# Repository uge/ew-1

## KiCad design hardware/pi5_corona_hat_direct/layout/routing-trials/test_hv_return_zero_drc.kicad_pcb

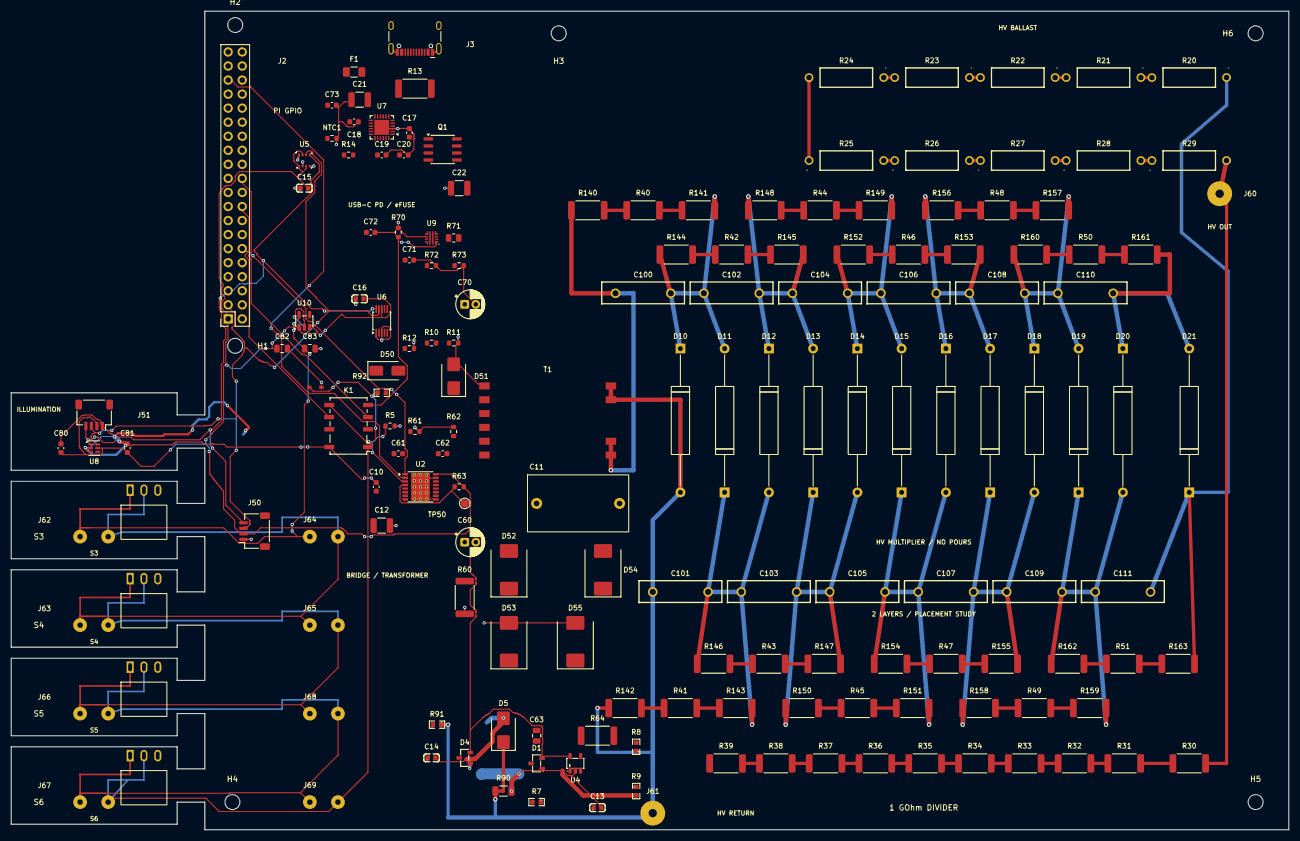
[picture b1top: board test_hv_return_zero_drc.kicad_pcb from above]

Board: 2 copper layers, 231.0 x 148.0 mm, 175 parts (0 on the bottom side), 108 nets.

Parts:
C10: 100nF 50V X7R 10%; C_0603_1608Metric
C11: 120nF 100V; Film_KYET_18x10mm_P15mm
C12: 10uF 50V X7R 10%; C_1210_3225Metric
C13, C14, C15, C16: 100nF; C0603
C17: 1uF 50V 10%; C_0603_1608Metric
C18, C20: 100nF 10%; C_0603_1608Metric
C19: 1uF 16V 10%; C_0603_1608Metric
C21: 4.7uF 50V 10%; C_1210_3225Metric
C22: 10uF 50V 10%; C_1210_3225Metric
C60: 33uF 50V 20%; CP_Radial_D5.0mm_P2.00mm
C61: 100nF 16V X7R 10%; C_0603_1608Metric
C62: 22nF 50V X7R 10%; C_0603_1608Metric
C63: 1nF 100V DNP; C_0805_2012Metric
C70: 22uF 50V 20%; CP_Radial_D5.0mm_P2.00mm
C71: 100nF 50V 10%; C_0603_1608Metric
C72: 2.2nF 50V 10%; C_0603_1608Metric
C73: 1uF 50V X7R 10%; C_0603_1608Metric
C80: 100nF 10V X7R; C_0603_1608Metric
C81: 1uF 10V X7R; C_0603_1608Metric
C82, C83: 2.2uF 16V X7R; C_0805_2012Metric
C100, C101, C102, C103, C104, C105, C106, C107, C108, C109, C110, C111: 1nF 6kV; CAP-TH_L15.0-W4.0-P10.00-D0.6
D1, D4: BAT54S; SOT-23-3_L2.9-W1.3-P1.90-LS2.4-BR
D3: 1N4148WS; D_SOD-323
D5: SMBJ15A; D_SMB
D10, D11, D12, D13, D14, D15, D16, D17, D18, D19, D20, D21: 2CL75; Sunmate_2CL75_D3_L12_P26
D50: VSSA310S-M3; D_SMA
D51: SMBJ22A; D_SMB
D52, D53, D54, D55: SS36 60V 3A; D_SMC
F1: 1A 30V PTC; Fuse_1206_3216Metric
H1, H2, H3, H4, H5, H6: MountingHole_2.7mm_M2.5
J2: Pi 5 HAT 2x20; PinSocket_2x20_P2.54mm_Vertical
J3: USB-C PD INPUT; USB_C_Receptacle_HCTL_HC-TYPE-C-16P-01A
J50: Qwiic HOST; JST_SH_SM04B-SRSS-TB_1x04-1MP_P1.00mm_Horizontal
J51: Qwiic MINI; JST_SH_SM04B-SRSS-TB_1x04-1MP_P1.00mm_Horizontal
J60: HV_OUT_WIRE; HV_Wire_Termination_1P
J61: HV_RETURN_WIRE; HV_Wire_Termination_1P
J62: S3_MINI; Solder_Pads_2P_P5.08
J63: S4_MINI; Solder_Pads_2P_P5.08
J64: S3_HOST; Solder_Pads_2P_P5.08
J65: S4_HOST; Solder_Pads_2P_P5.08
J66: S5_MINI; Solder_Pads_2P_P5.08
J67: S6_MINI; Solder_Pads_2P_P5.08
J68: S5_HOST; Solder_Pads_2P_P5.08
J69: S6_HOST; Solder_Pads_2P_P5.08
K1: G6K-2F-Y DC3; Relay_DPDT_Omron_G6K-2F-Y
MP1: Raspberry Pi 5 — DNP MECHANICAL; Raspberry_Pi_5_Mechanical
NTC1: 10k NTC; R_0603_1608Metric
Q1: AO4262E 60V; SO-8_3.9x4.9mm_P1.27mm
R5, R63: 10k; R_0603_1608Metric
R7: 1k; R0603
R8, R9: 82k; R0603
R10, R70: 100k 1%; R_0603_1608Metric
R11: 18k 1%; R_0603_1608Metric
R12: 100k; R_0603_1608Metric
R13: 5mR 1%; R_2512_6332Metric
R14: 6.2k; R_0603_1608Metric
R20, R21, R22, R23, R24, R25, R26, R27, R28, R29: 10M 3.5kV; RES-TH_BD3.5-L9.5-P13.50-D0.6
R30, R31, R32, R33, R34, R35, R36, R37, R38, R39, R40, R41, R42, R43, R44, R45, R46, R47, R48, R49, R50, R51, R140, R141, R142, R143, R144, R145, R146, R147, R148, R149, R150, R151, R152, R153, R154, R155, R156, R157, R158, R159, R160, R161, R162, R163: 100M 3kV; R_2512_6332Metric
R60: 1k 1W; R_2512_6332Metric
R61: 3.3k 1%; R_0603_1608Metric
R62: 62k 1%; R_0603_1608Metric
R64: 100R 1W DNP; R_2512_6332Metric
R71: 976k 0.1%; R_0805_2012Metric
R72: 56.2k 0.1%; R_0603_1608Metric
R73: 3.32k 1%; R_0603_1608Metric
R90: 10k PULSE 0.75W; R_1206_3216Metric
R91, R92: 10k; R0603
S3, S4, S5, S6: TK-0013-R; SW_TK-0013-R
T1: FL2015-4LD; Coilcraft_FL2015_Package1_SMT
TP50: DRV FAULT; TestPoint_Pad_D1.5mm
U2: DRV8876PWPR; HTSSOP-16-1EP_4.4x5mm_P0.65mm_EP3.4x5mm_Mask3x3mm_ThermalVi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
U4: TLV9001; SOT-23-5_L3.0-W1.7-P0.95-LS2.8-BR
U5: BME280; Bosch_LGA-8_2.5x2.5mm_P0.65mm_ClockwisePinNumbering
U6: ADS1115; TSSOP-10_3x3mm_P0.5mm
U7: AP33772S; QFN-24-1EP_4x4mm_P0.5mm_EP2.7x2.7mm
U8: TSL2591; AMS_TSL25911FN
U9: TPS259470LRPW; Texas_RPW0010A_VQFN-HR-10_2x2mm
U10: TPS7A0230PDBVR; SOT-23-5

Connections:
3V3: C15.2, C16.2, C80.1, C81.1, C82.1, D1.2, D4.2, J2.1, J50.2, J51.2, R63.1, U2.5, U2.16, U4.5, U5.2, U5.6, U5.8, U6.8, U8.5, U10.1, U10.3
/01_power_mcu/CC1: J3.A5, U7.17
/01_power_mcu/CC2: J3.B5, U7.16
/01_power_mcu/EFUSE_DVDT: C72.1, U9.7
/01_power_mcu/EFUSE_ILM: R73.1, U9.9
/01_power_mcu/EFUSE_OVLO: R71.2, R72.1, U9.2
/01_power_mcu/EN_DRV: R14.1, U7.23
/01_power_mcu/GATE: Q1.4, R12.1, R14.2
/01_power_mcu/IFB: C20.1, U7.15
/01_power_mcu/ISENP: F1.2, R13.1, U7.1
/01_power_mcu/OTP_NTC: NTC1.1, U7.13
/01_power_mcu/PD_VMON: R10.2, R11.1, U6.6
/01_power_mcu/SCL: J2.5, J50.4, J51.4, U5.4, U6.10, U7.5, U8.1
/01_power_mcu/SDA: J2.3, J50.3, J51.3, U5.3, U6.9, U7.4, U8.6
/01_power_mcu/USB_DN: J3.A7, J3.B7, U7.18
/01_power_mcu/USB_DP: J3.A6, J3.B6, U7.19
/01_power_mcu/V5V: C19.1, U7.20
/01_power_mcu/V18: C18.1, U7.12
/01_power_mcu/VBUS_IN: C17.1, C21.1, Q1.5, Q1.6, Q1.7, Q1.8, R13.2, U7.24
/01_power_mcu/VBUS_RAW: C73.1, F1.1, J3.A4, J3.A9, J3.B4, J3.B9, R10.1
/01_power_mcu/VIN_PD: C71.1, Q1.1, Q1.2, Q1.3, R71.1, U7.22, U9.5
/02_drive_transformer/DRV_A: C11.1, D52.2, D53.1, U2.8
/02_drive_transformer/DRV_B: C63.2, D54.2, D55.1, T1.5, U2.10
/02_drive_transformer/DRV_CPH: C62.1, U2.13
/02_drive_transformer/DRV_CPL: C62.2, U2.14
/02_drive_transformer/DRV_IMODE: R62.1, U2.7
/02_drive_transformer/DRV_IPROPI: R61.1, U2.6
/02_drive_transformer/DRV_VCP: C61.1, U2.12
/02_drive_transformer/DRV_nFAULT: R63.2, TP50.1, U2.4
/02_drive_transformer/HV_BRIDGE: C10.1, C12.1, C60.1, C61.2, D50.1, D51.1, D52.1, D54.1, R60.1, U2.11
/02_drive_transformer/PRI_A: C11.2, R64.1, T1.1
/03_multiplier/CW_P1: C100.2, C102.1, D10.1, D11.2, R141.2, R144.1
/03_multiplier/CW_P2: C102.2, C104.1, D12.1, D13.2, R145.2, R148.1
/03_multiplier/CW_P3: C104.2, C106.1, D14.1, D15.2, R149.2, R152.1
/03_multiplier/CW_P4: C106.2, C108.1, D16.1, D17.2, R153.2, R156.1
/03_multiplier/CW_P5: C108.2, C110.1, D18.1, D19.2, R157.2, R160.1
/03_multiplier/CW_S1: C101.2, C103.1, D11.1, D12.2, R143.2, R146.1
/03_multiplier/CW_S2: C103.2, C105.1, D13.1, D14.2, R147.2, R150.1
/03_multiplier/CW_S3: C105.2, C107.1, D15.1, D16.2, R151.2, R154.1
/03_multiplier/CW_S4: C107.2, C109.1, D17.1, D18.2, R155.2, R158.1
/03_multiplier/CW_S5: C109.2, C111.1, D19.1, D20.2, R159.2, R162.1
/04_sense_safety/HV_OUT: J60.1, R29.2, R30.1
/04_sense_safety/HV_SENSE_RAW: C13.1, R8.1, R39.2, U4.3
/04_sense_safety/LID_2: J63.2, J65.2, J66.1, J68.1, S4.2, S5.1
/04_sense_safety/LID_3: J66.2, J67.1, J68.2, J69.1, S5.2, S6.1
/04_sense_safety/LID_INT: J62.2, J63.1, J64.2, J65.1, S3.2, S4.1
/04_sense_safety/RELAY_COIL_POS: D3.1, J67.2, J69.2, K1.1, R92.1, S6.2
/DRV_IN1: J2.12, U2.1
/DRV_IN2: J2.35, U2.2
/DRV_SLEEP_CMD: J2.18, K1.6
/DRV_nSLEEP: K1.5, R5.1, U2.3
/HV_CURR_ADC: C14.1, D4.3, R91.2, U6.5
/HV_RAW: C111.2, D21.1, R20.1, R163.2
/HV_RETURN: C101.1, D5.1, D10.2, J61.1, R90.1, R91.1, R142.1, T1.9, T1.10
/HV_SENSE_ADC: D1.3, R7.2, U6.4
/INTERLOCK_OK: J2.16, R92.2
/SEC_A: C100.1, R140.1, T1.7, T1.8
/VIN_PROTECTED: C22.1, C70.1, D50.2, U9.6
BULK_CMD: J2.22, K1.3
BULK_EN: K1.4, R70.1, U9.1
COIL_3V: C83.1, J62.1, J64.1, S3.1, U10.5
GND: C10.2, C12.2, C13.2, C14.2, C15.1, C16.1, C17.2, C18.2, C19.2, C20.2, C21.2, C22.2, C60.2, C70.2, C71.2, C72.2, C73.2, C80.2, C81.2, C82.2, C83.2, D1.1, D3.2, D4.1, D5.2, D51.2, D53.2, D55.2, J2.6, J2.9, J2.14, J2.20, J2.25, J2.30, J2.34, J2.39, J3.A1, J3.A12, J3.B1, J3.B12, J3.SH, J50.1, J51.1, K1.8, NTC1.2, R5.2, R9.2, R11.2, R12.2, R60.2, R61.2, R62.2, R70.2, R72.2, R73.2, R90.2, T1.6, U2.9, U2.15, U2.17, U4.2, U5.1, U5.5, U5.7, U6.1, U6.3, U7.3, U7.25, U8.3, U9.8, U10.2
unnamed: C63.1, R64.2
unnamed: C110.2, D20.1, D21.2, R161.2
unnamed: R8.2, R9.1
unnamed: R20.2, R21.1
unnamed: R21.2, R22.1
unnamed: R22.2, R23.1
unnamed: R23.2, R24.1
unnamed: R24.2, R25.1
unnamed: R25.2, R26.1
unnamed: R26.2, R27.1
unnamed: R27.2, R28.1
unnamed: R28.2, R29.1
unnamed: R30.2, R31.1
unnamed: R31.2, R32.1
unnamed: R32.2, R33.1
unnamed: R33.2, R34.1
unnamed: R34.2, R35.1
unnamed: R35.2, R36.1
unnamed: R36.2, R37.1
unnamed: R37.2, R38.1
unnamed: R38.2, R39.1
unnamed: R40.1, R140.2
unnamed: R40.2, R141.1
unnamed: R41.1, R142.2
unnamed: R41.2, R143.1
unnamed: R42.1, R144.2
unnamed: R42.2, R145.1
unnamed: R43.1, R146.2
unnamed: R43.2, R147.1
unnamed: R44.1, R148.2
unnamed: R44.2, R149.1
unnamed: R45.1, R150.2
unnamed: R45.2, R151.1
unnamed: R46.1, R152.2
unnamed: R46.2, R153.1
unnamed: R47.1, R154.2
unnamed: R47.2, R155.1
unnamed: R48.1, R156.2
unnamed: R48.2, R157.1
unnamed: R49.1, R158.2
unnamed: R49.2, R159.1
unnamed: R50.1, R160.2
unnamed: R50.2, R161.1
unnamed: R51.1, R162.2
unnamed: R51.2, R163.1
unnamed: R7.1, U4.1, U4.4
